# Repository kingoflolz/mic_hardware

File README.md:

# Phased Array Microphone Hardware and Mechanical Designs

For more detail on the project see links below:

- [Blogpost](https://benwang.dev/2023/02/26/Phased-Array-Microphone.html)
- [Host software](https://github.com/kingoflolz/mic_host)
- [FPGA gateware](https://github.com/kingoflolz/mic_gateware)

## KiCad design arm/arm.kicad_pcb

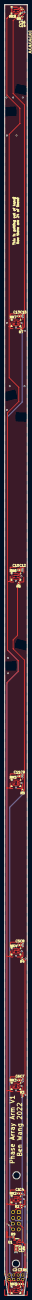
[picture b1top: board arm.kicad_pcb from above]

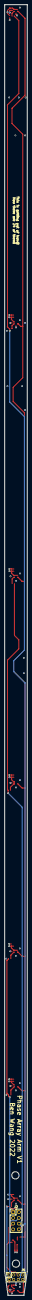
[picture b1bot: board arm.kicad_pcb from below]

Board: 4 copper layers, 10.0 x 570.0 mm, 40 parts (2 on the bottom side), 17 nets.

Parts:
C1, C2, C5, C6, C9, C10, C13, C14, C17: 10uF; C_0402_1005Metric
C3, C4, C7, C8, C11, C12, C15, C16, C18: 100nF; C_0402_1005Metric
H1, H2: MountingHole; MountingHole_3.2mm_M3
J1: Conn_02x04_Counter_Clockwise; PinSocket_2x04_P2.00mm_Vertical
J2: Conn_02x04_Counter_Clockwise; PinHeader_2x04_P2.54mm_Vertical
MK1, MK2, MK3, MK4, MK5, MK6, MK7, MK8: MSM261D4030H1CPM
R1, R2, R3, R4, R5, R6, R7, R8, R9: 56R; R_0402_1005Metric
U1: SN74LVC1G14DBV; SOT-23-5

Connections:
+3.3V: C1.1, C2.1, C3.1, C4.1, C5.1, C6.1, C7.1, C8.1, C9.1, C10.1, C11.1, C12.1, C13.1, C14.1, C15.1, C16.1, C17.1, C18.1, J1.1, J2.1, MK1.1 (VDD), MK2.1 (VDD), MK2.2 (L/R), MK3.1 (VDD), MK4.1 (VDD), MK4.2 (L/R), MK5.1 (VDD), MK6.1 (VDD), MK6.2 (L/R), MK7.1 (VDD), MK8.1 (VDD), MK8.2 (L/R), U1.5 (VCC)
/CLK: J1.5, J2.5, U1.2
/dual mic1/DOUT: J1.2, J2.2, R1.2, R2.2
/dual mic2/DOUT: J1.4, J2.4, R3.2, R4.2
/dual mic3/DOUT: J1.6, J2.6, R5.2, R6.2
/dual mic4/DOUT: J1.8, J2.8, R7.2, R8.2
CLK_DRV: MK1.3 (CLOCK), MK2.3 (CLOCK), MK3.3 (CLOCK), MK4.3 (CLOCK), MK5.3 (CLOCK), MK6.3 (CLOCK), MK7.3 (CLOCK), MK8.3 (CLOCK), R9.2
GND: C1.2, C2.2, C3.2, C4.2, C5.2, C6.2, C7.2, C8.2, C9.2, C10.2, C11.2, C12.2, C13.2, C14.2, C15.2, C16.2, C17.2, C18.2, J1.3, J1.7, J2.3, J2.7, MK1.2 (L/R), MK1.5 (GND), MK2.5 (GND), MK3.2 (L/R), MK3.5 (GND), MK4.5 (GND), MK5.2 (L/R), MK5.5 (GND), MK6.5 (GND), MK7.2 (L/R), MK7.5 (GND), MK8.5 (GND), U1.3 (GND)
unnamed: MK1.4 (DATA), R1.1
unnamed: MK2.4 (DATA), R2.1
unnamed: MK3.4 (DATA), R3.1
unnamed: MK4.4 (DATA), R4.1
unnamed: MK5.4 (DATA), R5.1
unnamed: MK6.4 (DATA), R6.1
unnamed: MK7.4 (DATA), R7.1
unnamed: MK8.4 (DATA), R8.1
unnamed: R9.1, U1.4

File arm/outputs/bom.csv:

Comment,Designator,Footprint,LCSC
10uF,"C1,C2,C5,C6,C9,C10,C13,C14,C17",Capacitor_SMD:C_0402_1005Metric,
100nF,"C3,C4,C7,C8,C11,C12,C15,C16,C18",Capacitor_SMD:C_0402_1005Metric,
Conn_02x04_Counter_Clockwise,J1,Connector_PinSocket_2.00mm:PinSocket_2x04_P2.00mm_Vertical,
Conn_02x04_Counter_Clockwise,J2,Connector_PinHeader_2.54mm:PinHeader_2x04_P2.54mm_Vertical,
MSM261D4030H1CPM,"MK1,MK2,MK3,MK4,MK5,MK6,MK7,MK8",MSM261D4030H1CPM:MSM261D4030H1CPM,
56R,"R1,R2,R3,R4,R5,R6,R7,R8,R9",Resistor_SMD:R_0402_1005Metric,
SN74LVC1G14DBV,U1,Package_TO_SOT_SMD:SOT-23-5,

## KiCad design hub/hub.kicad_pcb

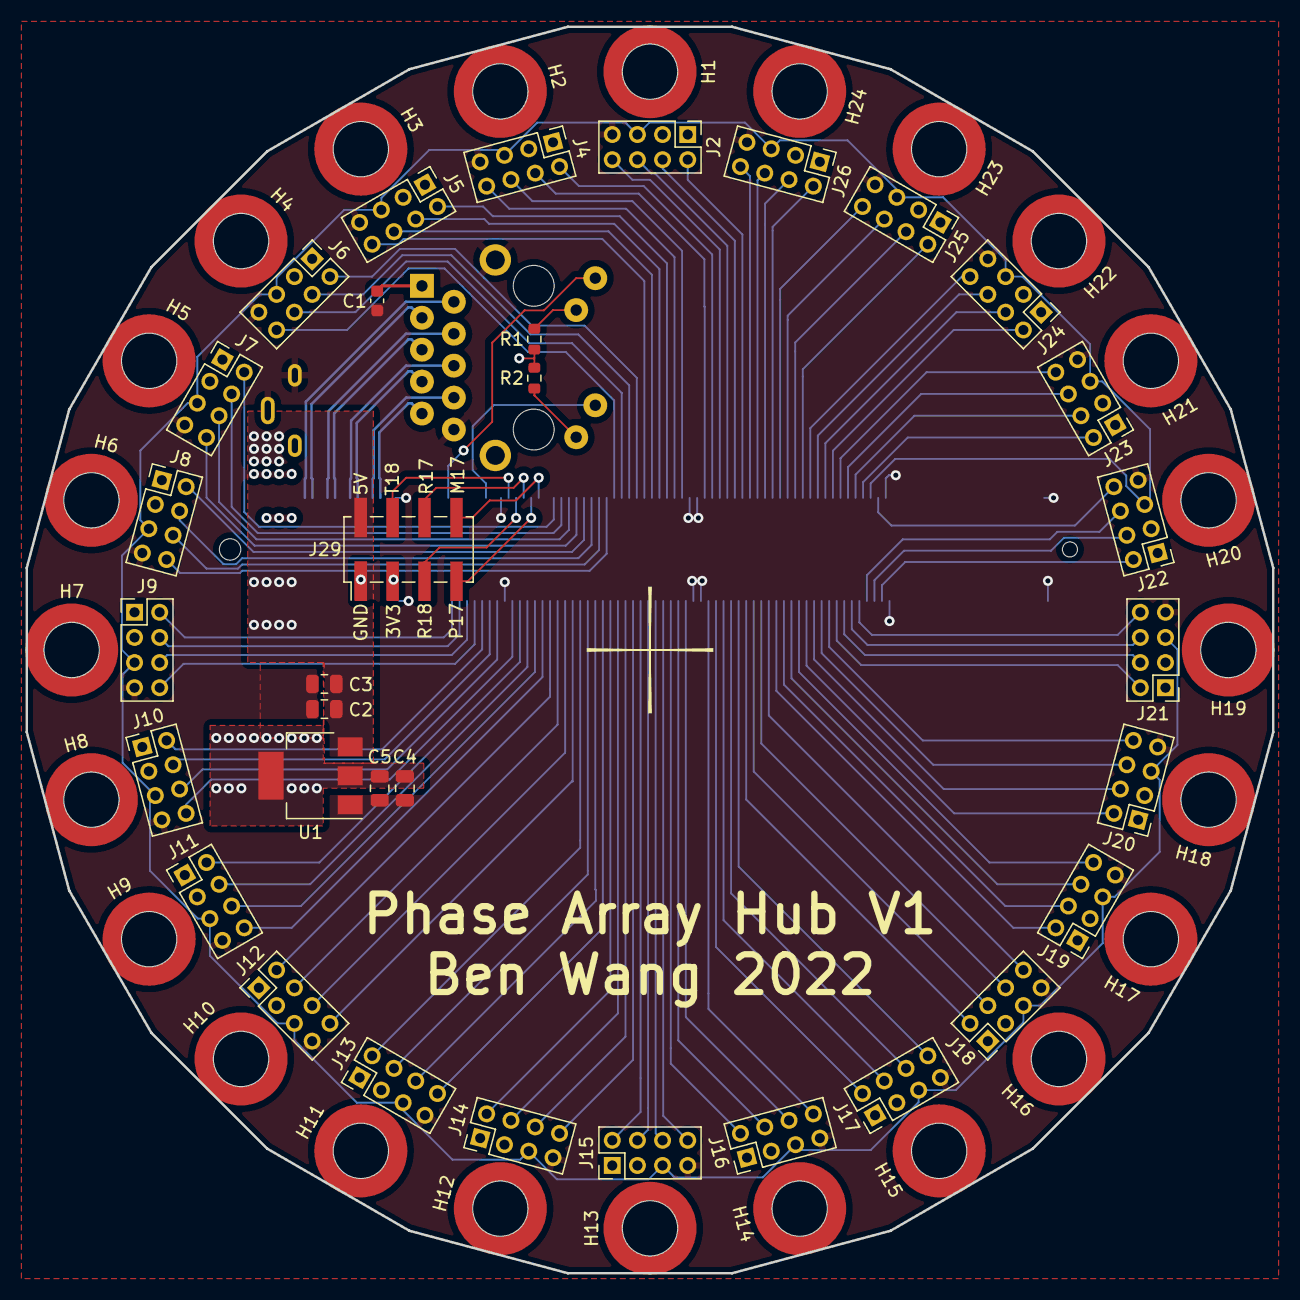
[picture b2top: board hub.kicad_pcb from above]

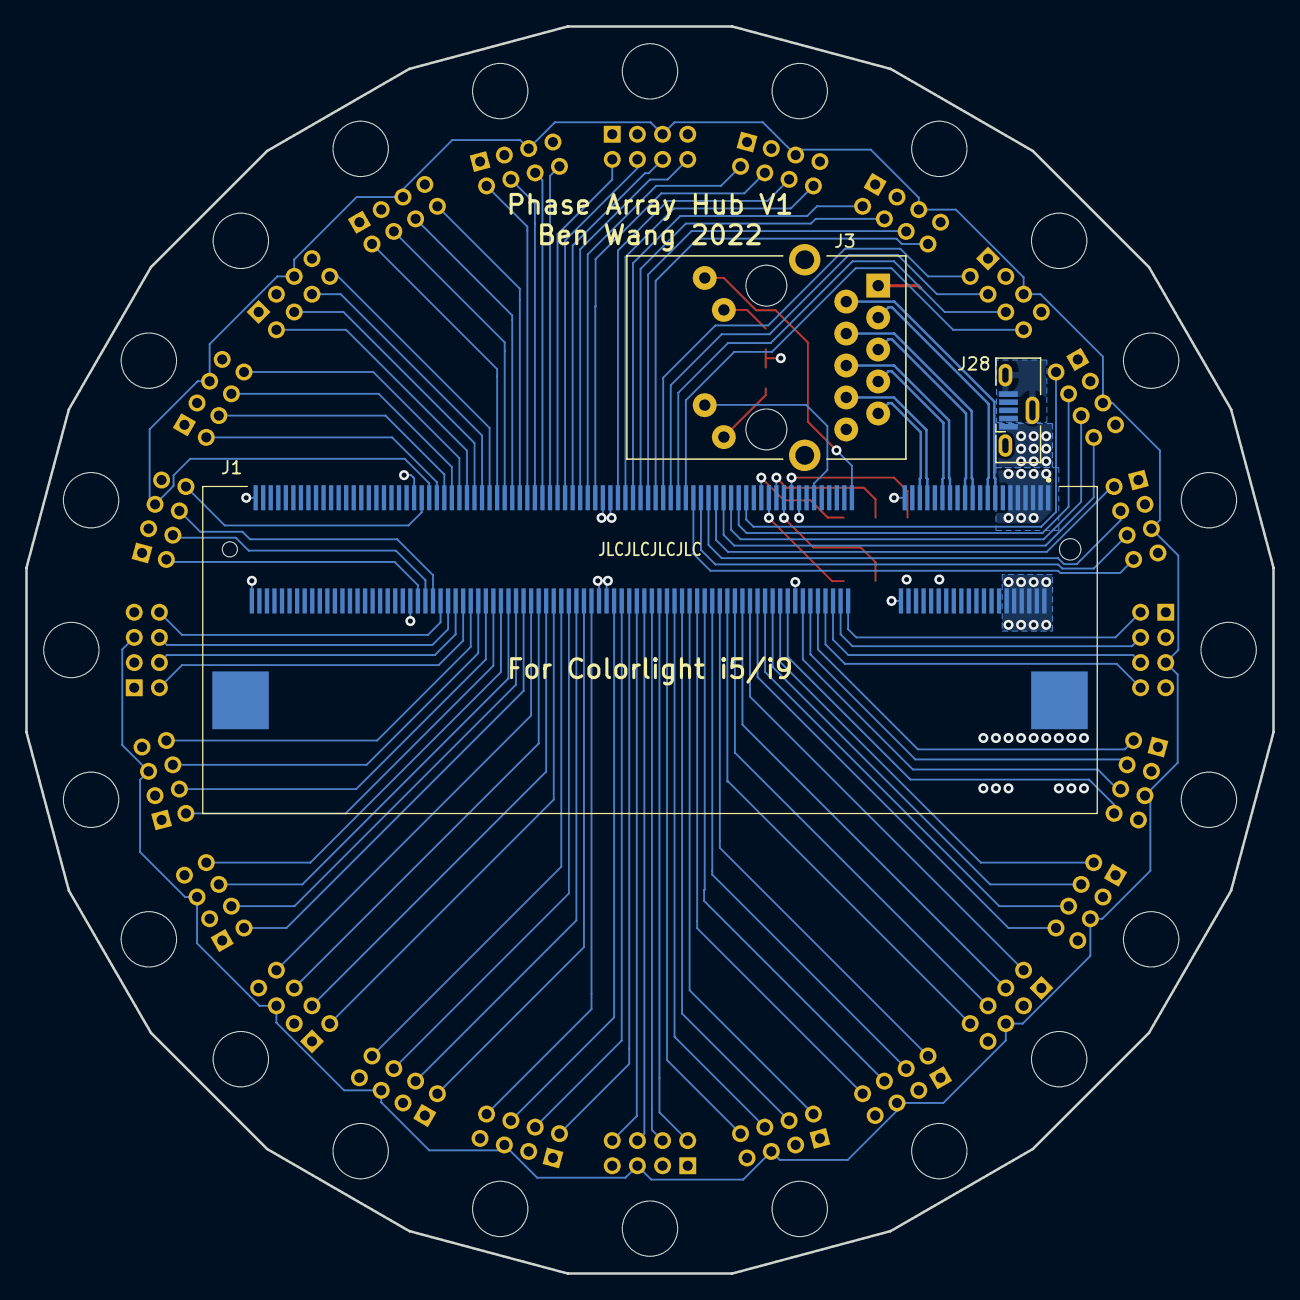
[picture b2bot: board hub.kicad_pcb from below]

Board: 4 copper layers, 99.1 x 99.1 mm, 60 parts (3 on the bottom side), 118 nets.

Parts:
C1: 0.1uF; C_0603_1608Metric
C2, C3, C4, C5: 22uF; C_0805_2012Metric
H1, H2, H3, H4, H5, H6, H7, H8, H9, H10, H11, H12, H13, H14, H15, H16, H17, H18, H19, H20, H21, H22, H23, H24: MountingHole; Mounting_Wuerth_WA-SMSI-M3_H8mm_9774080360
J1: SODIMM-200_Split; 14730054
J2, J4, J5, J6, J7, J8, J9, J10, J11, J12, J13, J14, J15, J16, J17, J18, J19, J20, J21, J22, J23, J24, J25, J26: Conn_02x03_Counter_Clockwise; PinHeader_2x04_P2.00mm_Vertical
J3: RB1-125B8G1A; RJ45_UDE_RB1-125B8G1A
J28: USB_B_Micro; USB_Micro-B_Molex-105133-0001
J29: Conn_02x03_Counter_Clockwise; PinHeader_2x04_P2.54mm_Vertical_SMD
R1, R2: 10K; R_0603_1608Metric
U1: AMS1117-3.3; SOT-223-3_TabPin2

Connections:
+3.3V: C4.1, C5.1, J2.1, J4.1, J5.1, J6.1, J7.1, J8.1, J9.1, J10.1, J11.1, J12.1, J13.1, J14.1, J15.1, J16.1, J17.1, J18.1, J19.1, J20.1, J21.1, J22.1, J23.1, J24.1, J25.1, J26.1, J29.3, R1.1, R2.1, U1.2 (VO)
+5V: C2.1, C3.1, J1.2, J1.4, J1.6, J1.8, J1.10, J1.12, J28.1 (VBUS), J29.2, U1.3 (VI)
/DBG_1: J1.57, J29.4
/DBG_2: J1.59, J29.5
/DBG_3: J1.61, J29.6
/DBG_4: J1.63, J29.7
/DBG_5: J1.65, J29.8
/G_LED: J1.41, J3.L4
/Y_LED: J1.51, J3.L2
/channel1/CH1_2: J1.119, J2.2
/channel1/CH3_4: J1.117, J2.4
/channel1/CH5_6: J1.115, J2.6
/channel1/CH7_8: J1.113, J2.8
/channel2/CH1_2: J1.111, J4.2
/channel2/CH3_4: J1.109, J4.4
/channel2/CH5_6: J1.103, J4.6
/channel2/CH7_8: J1.101, J4.8
/channel3/CH1_2: J1.99, J5.2
/channel3/CH3_4: J1.97, J5.4
/channel3/CH5_6: J1.95, J5.6
/channel3/CH7_8: J1.93, J5.8
/channel4/CH1_2: J1.91, J6.2
/channel4/CH3_4: J1.89, J6.4
/channel4/CH5_6: J1.87, J6.6
/channel4/CH7_8: J1.85, J6.8
/channel5/CH1_2: J1.69, J7.2
/channel5/CH3_4: J1.71, J7.4
/channel5/CH5_6: J1.73, J7.6
/channel5/CH7_8: J1.75, J7.8
/channel6/CH1_2: J1.77, J8.2
/channel6/CH3_4: J1.79, J8.4
/channel6/CH5_6: J1.81, J8.6
/channel6/CH7_8: J1.83, J8.8
/channel7/CH1_2: J1.42, J9.2
/channel7/CH3_4: J1.44, J9.4
/channel7/CH5_6: J1.46, J9.6
/channel7/CH7_8: J1.48, J9.8
/channel8/CH1_2: J1.50, J10.2
/channel8/CH3_4: J1.52, J10.4
/channel8/CH5_6: J1.54, J10.6
/channel8/CH7_8: J1.58, J10.8
/channel9/CH1_2: J1.60, J11.2
/channel9/CH3_4: J1.62, J11.4
/channel9/CH5_6: J1.64, J11.6
/channel9/CH7_8: J1.66, J11.8
/channel10/CH1_2: J1.68, J12.2
/channel10/CH3_4: J1.70, J12.4
/channel10/CH5_6: J1.72, J12.6
/channel10/CH7_8: J1.74, J12.8
/channel11/CH1_2: J1.76, J13.2
/channel11/CH3_4: J1.78, J13.4
/channel11/CH5_6: J1.80, J13.6
/channel11/CH7_8: J1.82, J13.8
/channel12/CH1_2: J1.84, J14.2
/channel12/CH3_4: J1.86, J14.4
/channel12/CH5_6: J1.88, J14.6
/channel12/CH7_8: J1.90, J14.8
/channel13/CH1_2: J1.92, J15.2
/channel13/CH3_4: J1.94, J15.4
/channel13/CH5_6: J1.96, J15.6
/channel13/CH7_8: J1.98, J15.8
/channel14/CH1_2: J1.100, J16.2
/channel14/CH3_4: J1.102, J16.4
/channel14/CH5_6: J1.104, J16.6
/channel14/CH7_8: J1.110, J16.8
/channel15/CH1_2: J1.112, J17.2
/channel15/CH3_4: J1.114, J17.4
/channel15/CH5_6: J1.116, J17.6
/channel15/CH7_8: J1.118, J17.8
/channel16/CH1_2: J1.120, J18.2
/channel16/CH3_4: J1.122, J18.4
/channel16/CH5_6: J1.124, J18.6
/channel16/CH7_8: J1.126, J18.8
/channel17/CH1_2: J1.128, J19.2
/channel17/CH3_4: J1.130, J19.4
/channel17/CH5_6: J1.132, J19.6
/channel17/CH7_8: J1.134, J19.8
/channel18/CH1_2: J1.136, J20.2
/channel18/CH3_4: J1.138, J20.4
/channel18/CH5_6: J1.140, J20.6
/channel18/CH7_8: J1.142, J20.8
/channel19/CH1_2: J1.144, J21.2
/channel19/CH3_4: J1.146, J21.4
/channel19/CH5_6: J1.148, J21.6
/channel19/CH7_8: J1.150, J21.8
/channel20/CH1_2: J1.156, J22.2
/channel20/CH3_4: J1.154, J22.4
/channel20/CH5_6: J1.152, J22.6
/channel20/CH7_8: J1.155, J22.8
/channel21/CH1_2: J1.151, J23.2
/channel21/CH3_4: J1.149, J23.4
/channel21/CH5_6: J1.147, J23.6
/channel21/CH7_8: J1.145, J23.8
/channel22/CH1_2: J1.143, J24.2
/channel22/CH3_4: J1.141, J24.4
/channel22/CH5_6: J1.139, J24.6
/channel22/CH7_8: J1.137, J24.8
/channel23/CH1_2: J1.135, J25.2
/channel23/CH3_4: J1.133, J25.4
/channel23/CH5_6: J1.131, J25.6
/channel23/CH7_8: J1.129, J25.8
/channel24/CH1_2: J1.127, J26.2
/channel24/CH3_4: J1.125, J26.4
/channel24/CH5_6: J1.123, J26.6
/channel24/CH7_8: J1.121, J26.8
/ethernet/ETH_1+: J1.15, J3.R2 (TD1+)
/ethernet/ETH_1-: J1.17, J3.R3 (TD1-)
/ethernet/ETH_2+: J1.21, J3.R4 (TD2+)
/ethernet/ETH_2-: J1.23, J3.R5 (TD2-)
/ethernet/ETH_3+: J1.27, J3.R6 (TD3+)
/ethernet/ETH_3-: J1.29, J3.R7 (TD3-)
/ethernet/ETH_4+: J1.33, J3.R8 (TD4+)
/ethernet/ETH_4-: J1.35, J3.R9 (TD4-)
CLK: J1.153, J2.5, J4.5, J5.5, J6.5, J7.5, J8.5, J9.5, J10.5, J11.5, J12.5, J13.5, J14.5, J15.5, J16.5, J17.5, J18.5, J19.5, J20.5, J21.5, J22.5, J23.5, J24.5, J25.5, J26.5
GND: C1.2, C2.2, C3.2, C4.2, C5.2, J1.1, J1.3, J1.5, J1.7, J1.9, J1.11, J1.39, J1.40, J1.55, J1.56, J1.105, J1.106, J1.107, J1.108, J1.157, J1.158, J1.199, J1.200, J2.3, J2.7, J3.R10 (GND), J3.SH, J4.3, J4.7, J5.3, J5.7, J6.3, J6.7, J7.3, J7.7, J8.3, J8.7, J9.3, J9.7, J10.3, J10.7, J11.3, J11.7, J12.3, J12.7, J13.3, J13.7, J14.3, J14.7, J15.3, J15.7, J16.3, J16.7, J17.3, J17.7, J18.3, J18.7, J19.3, J19.7, J20.3, J20.7, J21.3, J21.7, J22.3, J22.7, J23.3, J23.7, J24.3, J24.7, J25.3, J25.7, J26.3, J26.7, J28.5 (GND), J28.6 (Shield), J29.1, U1.1 (GND)
unnamed: C1.1, J3.R1 (CT)
unnamed: J3.L1, R2.2
unnamed: J3.L3, R1.2
